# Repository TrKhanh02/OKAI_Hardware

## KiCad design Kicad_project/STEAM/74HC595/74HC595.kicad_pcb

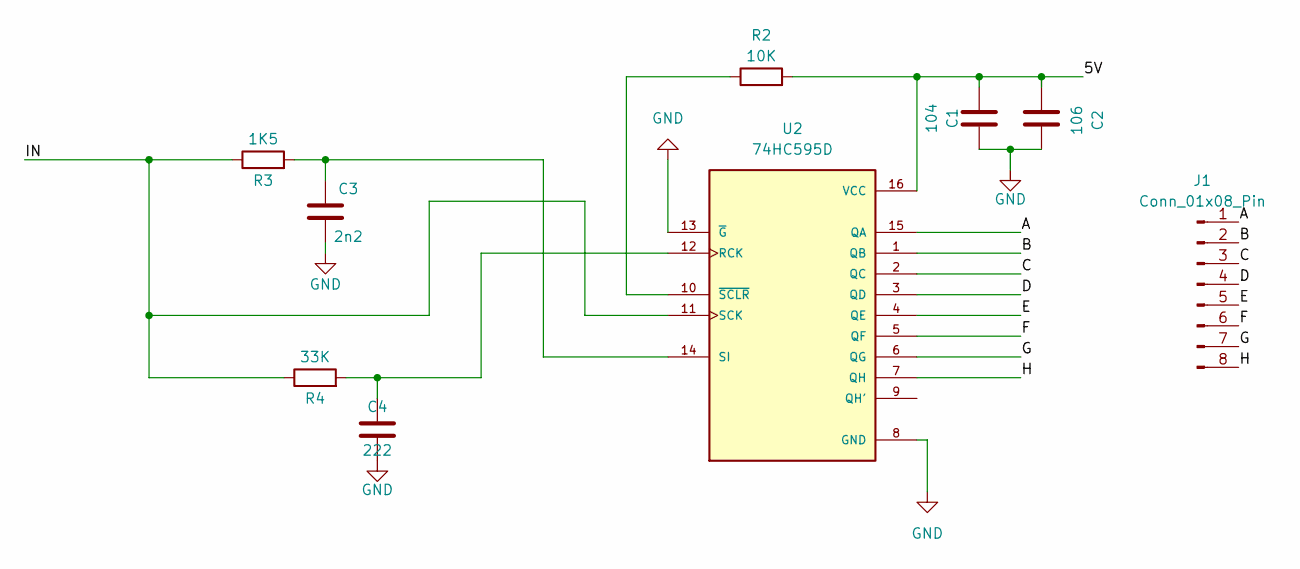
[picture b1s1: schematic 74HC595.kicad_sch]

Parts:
C1: 104; C_0805_2012Metric
C2: 106; C_0805_2012Metric
C3: 2n2; C_0805_2012Metric
C4: 222; C_0805_2012Metric
J1: Conn_01x08_Pin; PinHeader_1x08_P2.54mm_Vertical
R2: 10K; R_0805_2012Metric
R3: 1K5; R_0805_2012Metric
R4: 33K; R_0805_2012Metric
U2: 74HC595D; SOP127P600X175-16N; PARTREV 4.0

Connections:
/5V: C1.1, C2.1, R2.2, U2.16 (VCC)
/A: J1.1, U2.15 (QA)
/B: J1.2, U2.1 (QB)
/C: J1.3, U2.2 (QC)
/D: J1.4, U2.3 (QD)
/E: J1.5, U2.4 (QE)
/F: J1.6, U2.5 (QF)
/G: J1.7, U2.6 (QG)
/H: J1.8, U2.7 (QH)
/IN: R3.1, R4.1, U2.11 (SCK)
GND: C1.2, C2.2, C3.1, C4.1, U2.8 (GND), U2.13 (~G)
unnamed: C4.2, R4.2, U2.12 (RCK)
unnamed: C3.2, R3.2, U2.14 (SI)
unnamed: R2.1, U2.10 (~SCLR)

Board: 2 copper layers, 9 parts (0 on the bottom side), 14 nets, no tracks yet.

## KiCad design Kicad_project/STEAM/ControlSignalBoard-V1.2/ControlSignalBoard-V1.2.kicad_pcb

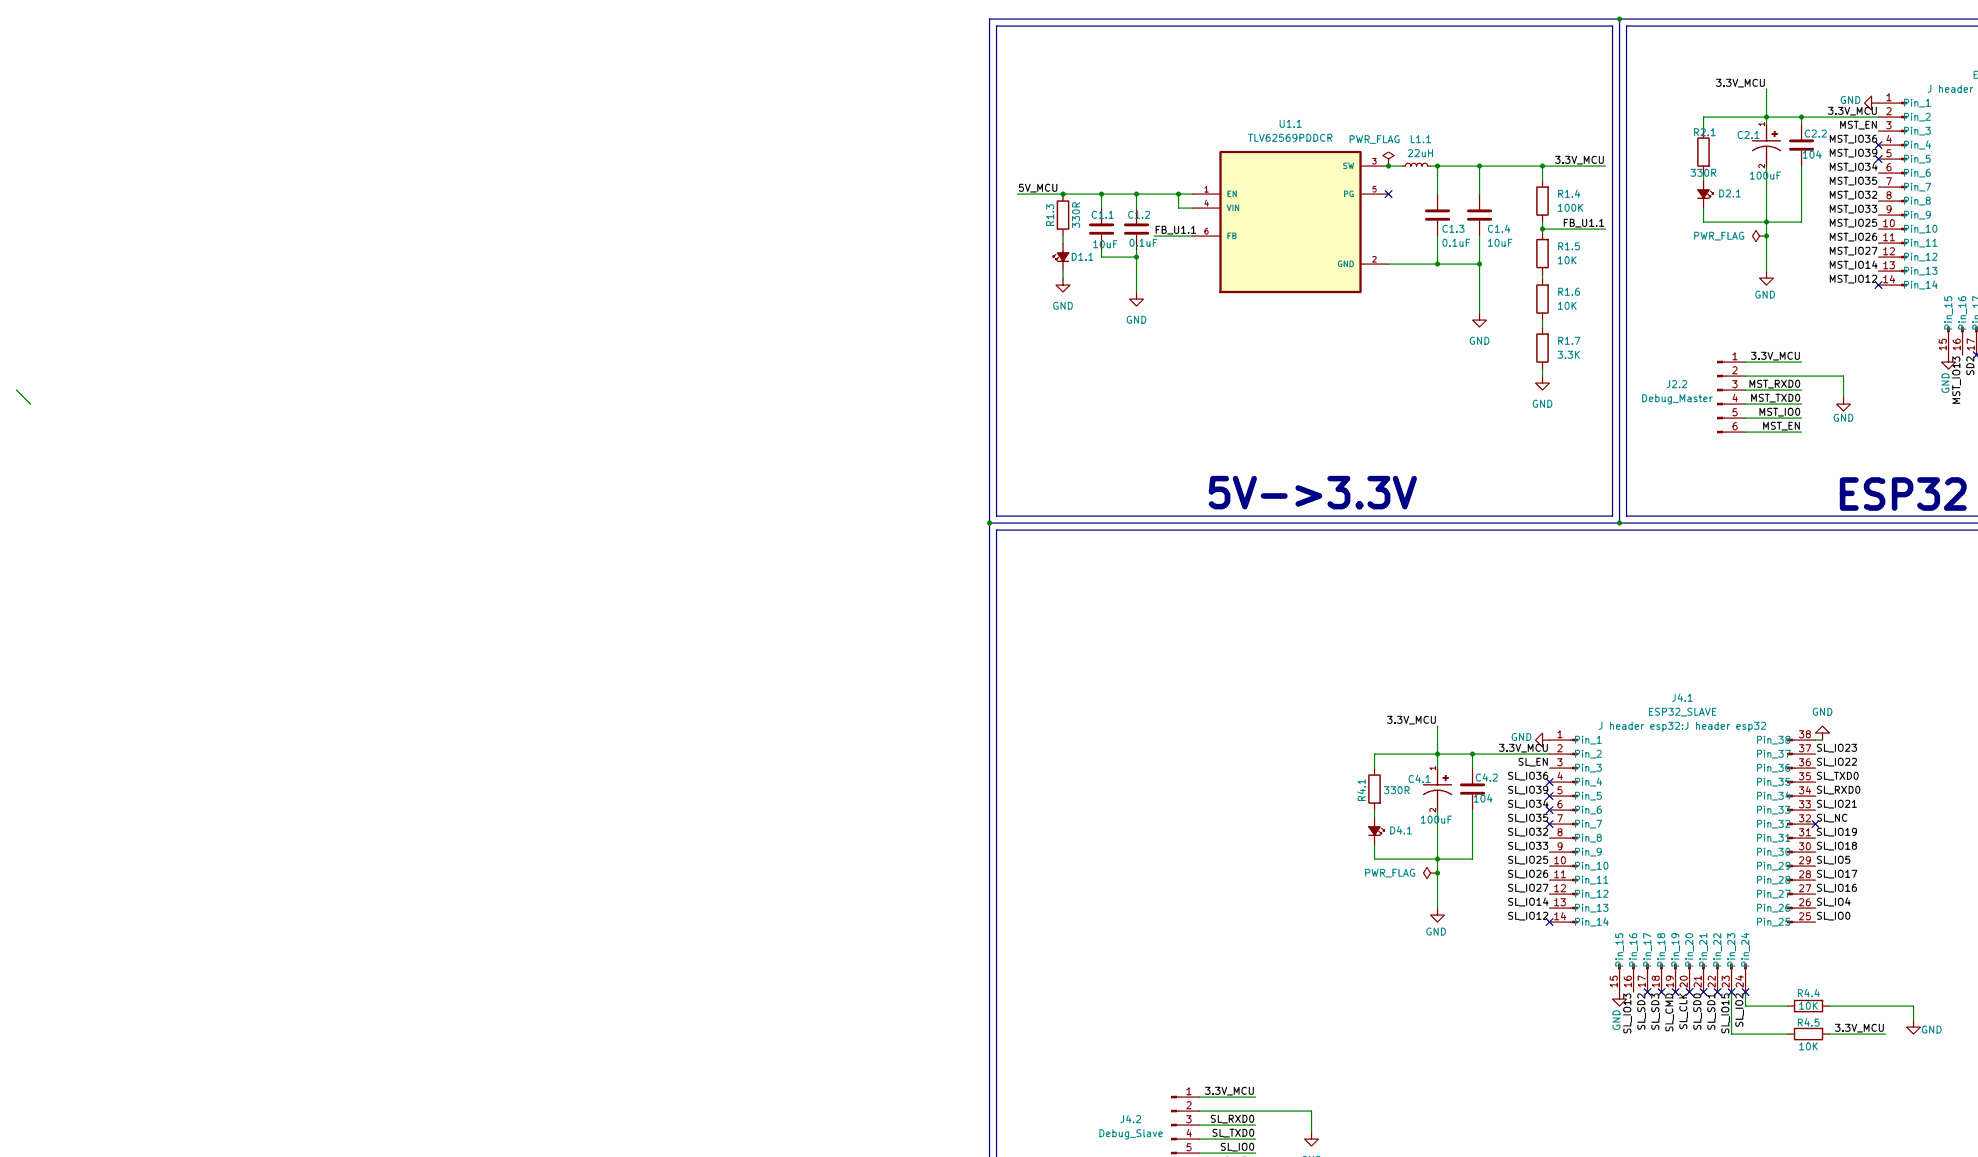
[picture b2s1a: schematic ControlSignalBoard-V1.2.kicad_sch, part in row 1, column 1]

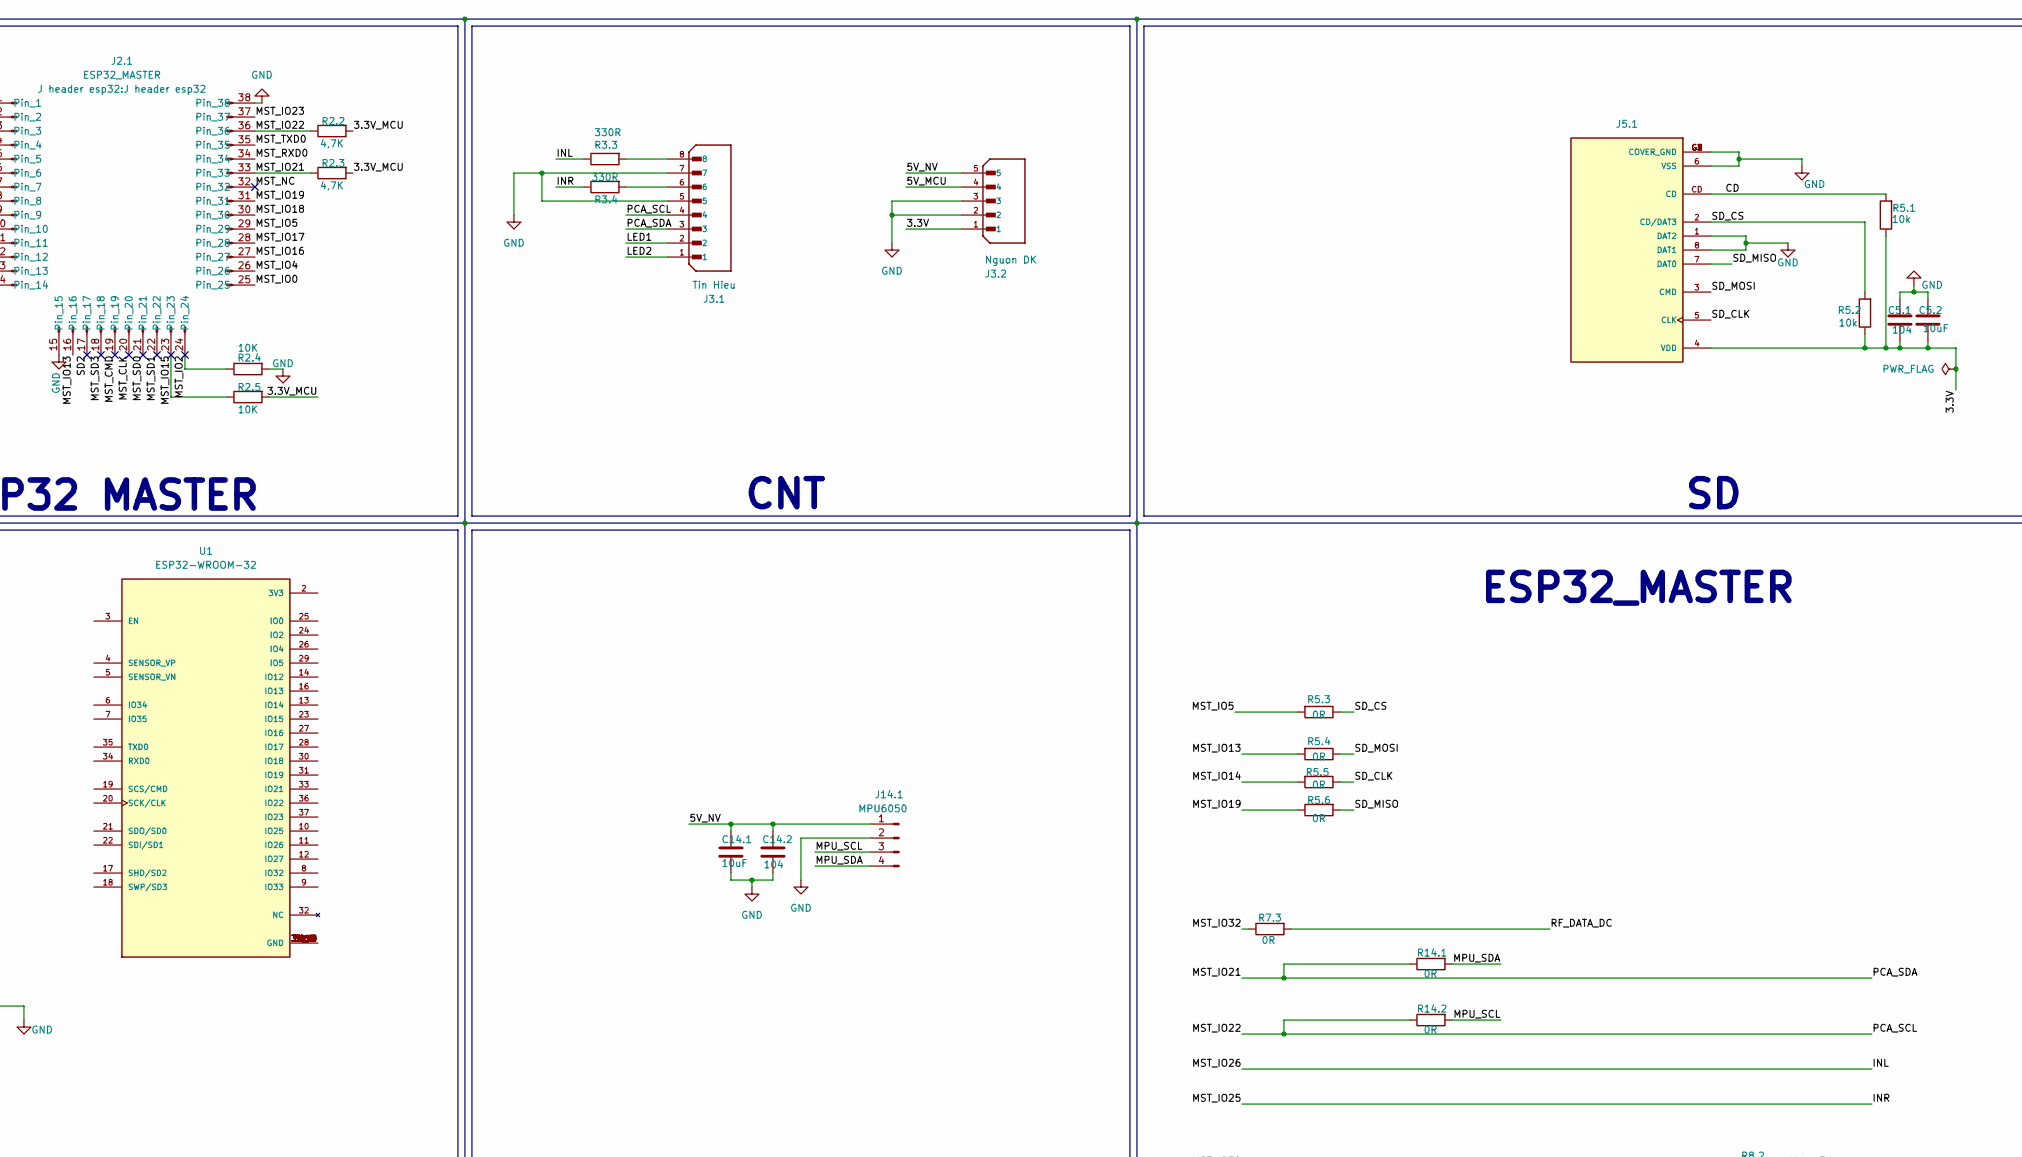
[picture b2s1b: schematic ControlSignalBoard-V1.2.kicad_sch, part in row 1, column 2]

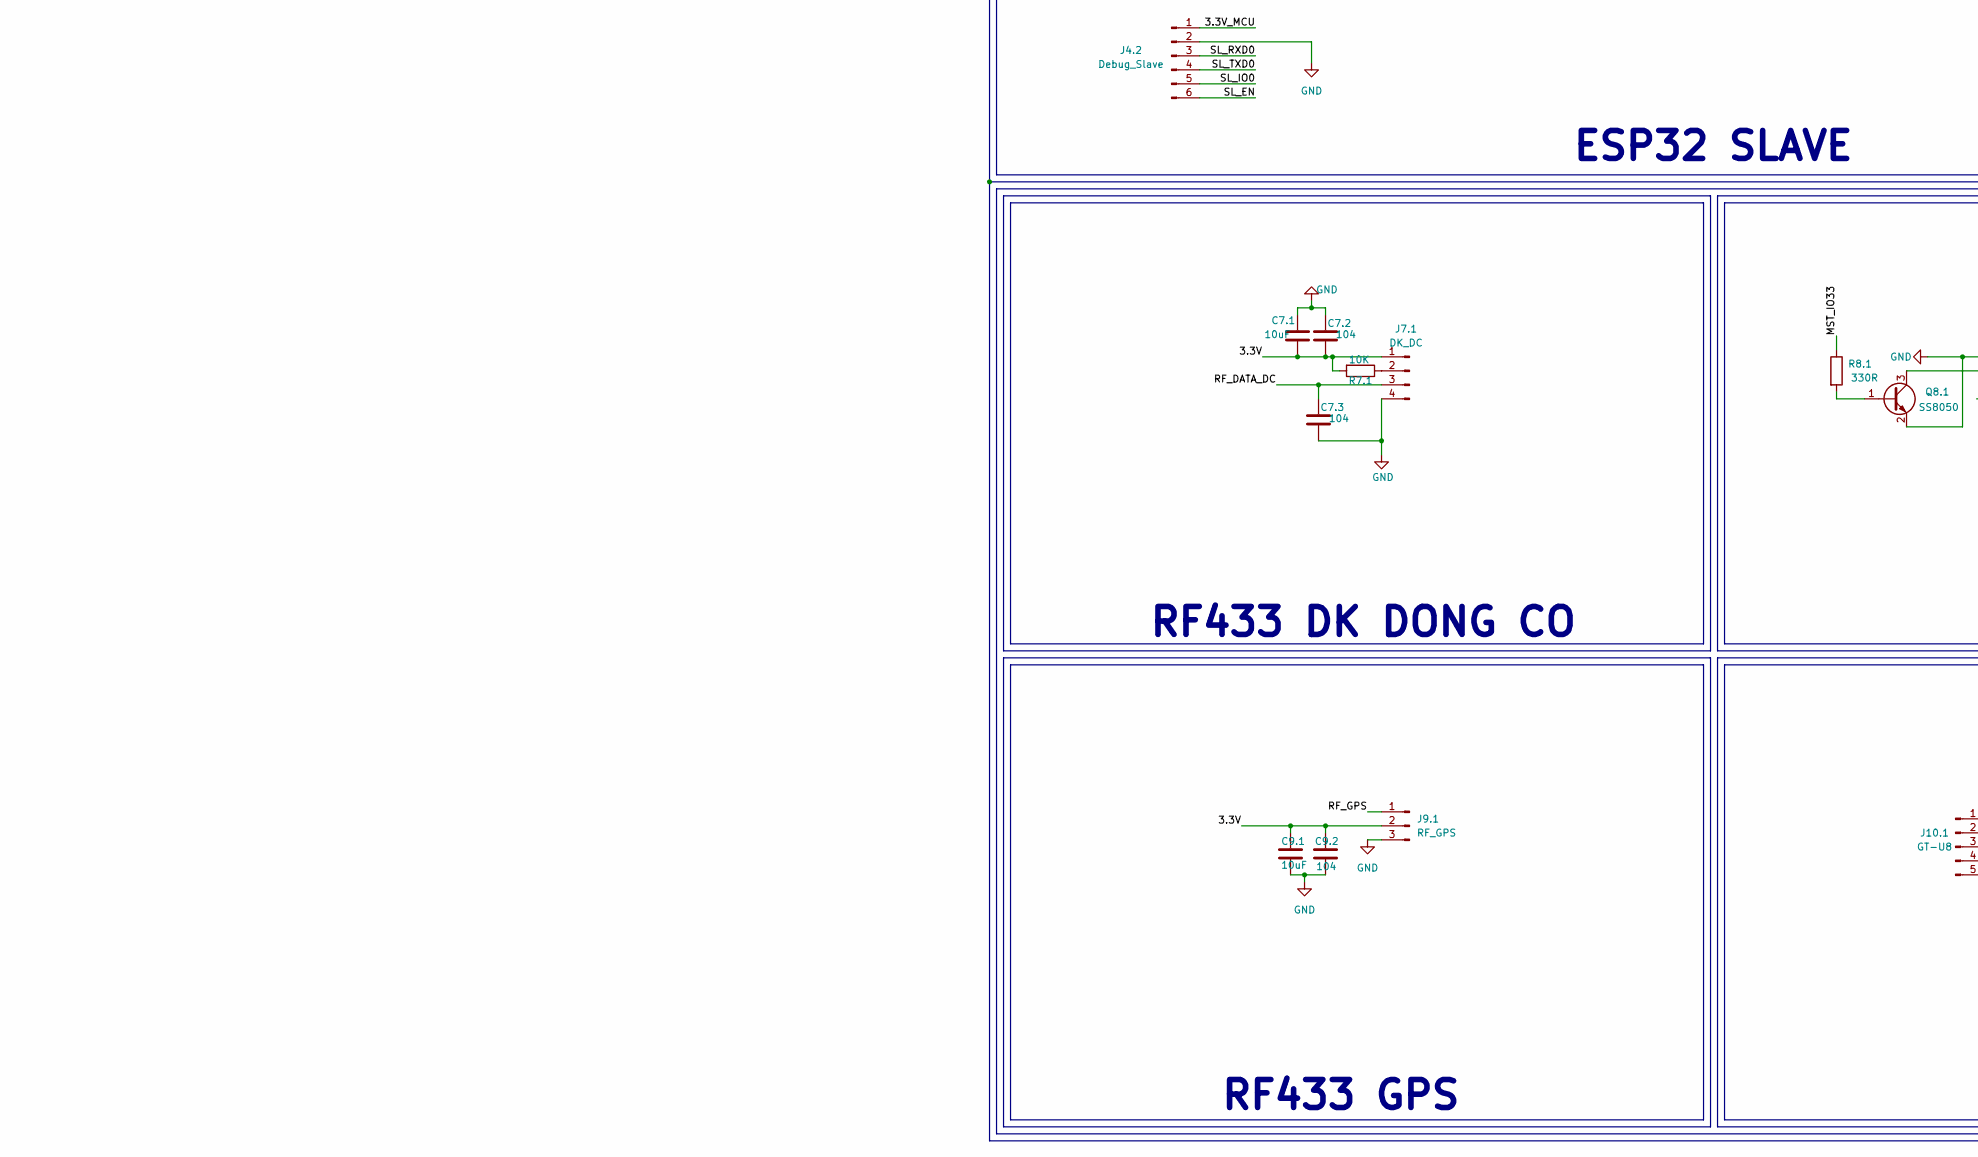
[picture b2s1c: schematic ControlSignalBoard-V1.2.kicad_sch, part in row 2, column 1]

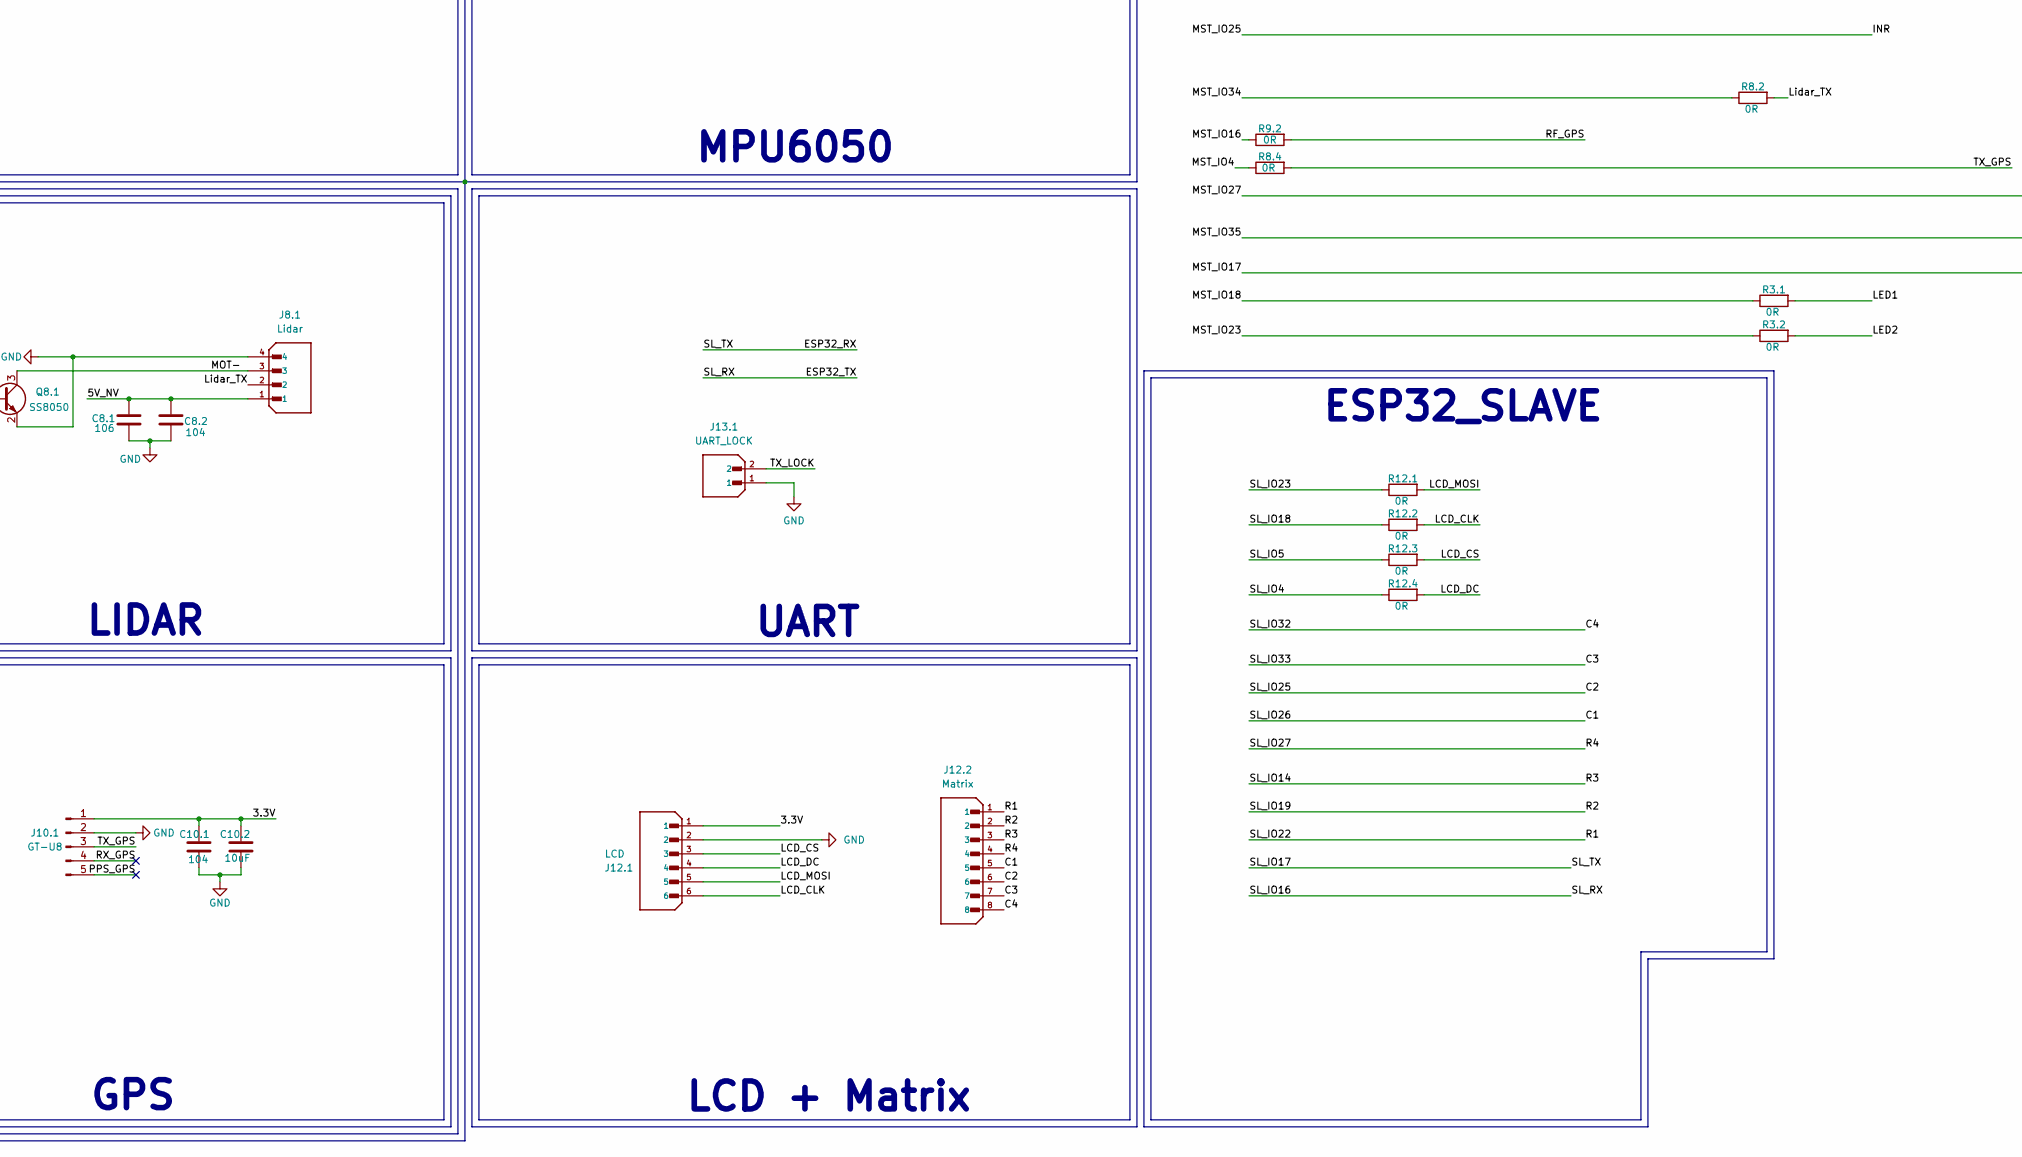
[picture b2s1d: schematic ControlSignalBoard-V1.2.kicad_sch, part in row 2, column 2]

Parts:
C1.1, C1.4: 10uF; C_0805_2012Metric
C1.2, C1.3: 0.1uF; C_0805_2012Metric
C2.1, C4.1: 100uF; CAPMP3216X180N; PARTREV 031320
C2.2, C4.2, C5.1, C7.2, C7.3, C8.2, C9.2, C10.1, C14.2: 104; C_0805_2012Metric_Pad1.18x1.45mm_HandSolder
C5.2, C7.1, C9.1, C10.2, C14.1: 10uF; C_0805_2012Metric_Pad1.18x1.45mm_HandSolder
C8.1: 106; C_0805_2012Metric_Pad1.18x1.45mm_HandSolder
D1.1, D2.1, D4.1: LED_Small_Filled; LED_0805_2012Metric_Pad1.15x1.40mm_HandSolder
J2.1: ESP32_MASTER; J header esp32
J2.2: Debug_Master; PinSocket_1x06_P2.54mm_Vertical
J3.1: Tin Hieu; JST_B8B-XH-A_LF__SN_; PARTREV 7/4/21
J3.2: Nguon DK; JST_B5B-XH-A; PARTREV 7/4/21
J4.1: ESP32_SLAVE; J header esp32
J4.2: Debug_Slave; PinSocket_1x06_P2.54mm_Vertical
J5.1: SD; CUI_MSD-1-A; PARTREV 1.0
J7.1: DK_DC; PinSocket_1x04_P2.54mm_Vertical
J8.1: Lidar; JST_B4B-XH-A_LF__SN_; PARTREV 7/4/21
J9.1: RF_GPS; PinSocket_1x03_P2.54mm_Vertical
J10.1: GT-U8; PinSocket_1x05_P2.54mm_Vertical
J12.1: LCD; JST_B6B-XH-A_LF__SN_; PARTREV 7/4/21
J12.2: Matrix; JST_B8B-XH-A_LF__SN_; PARTREV 7/4/21
J13.1: UART_LOCK; JST_B2B-XH-A_LF__SN_; PARTREV N/A
J14.1: MPU6050; PinSocket_1x04_P2.54mm_Vertical
L1.1: 22uH; L_Ferrocore_DLG-0705
Q8.1: SS8050; SOT-23
R1.3, R2.1, R3.3, R3.4, R4.1, R8.1: 330R; R_0805_2012Metric_Pad1.20x1.40mm_HandSolder
R1.4: 100K; R_0805_2012Metric
R1.5, R1.6: 10K; R_0805_2012Metric
R1.7: 3.3K; R_0805_2012Metric
R2.2, R2.3: 4,7K; R_0805_2012Metric_Pad1.20x1.40mm_HandSolder
R2.4, R2.5, R4.4, R4.5, R7.1: 10K; R_0805_2012Metric_Pad1.20x1.40mm_HandSolder
R3.1, R3.2, R5.3, R5.4, R5.5, R5.6, R7.3, R8.2, R8.4, R9.2, R12.1, R12.2, R12.3, R12.4, R14.1, R14.2: 0R; R_0805_2012Metric_Pad1.20x1.40mm_HandSolder
R5.1, R5.2: 10k; R_0805_2012Metric_Pad1.20x1.40mm_HandSolder
U1: ESP32-WROOM-32; MODULE_ESP32-WROOM-32
U1.1: TLV62569PDDCR; SOT95P280X110-6N

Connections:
/3.3V: C5.1.1, C5.2.1, C7.1.2, C7.2.2, C9.1.1, C9.2.1, C10.1.1, C10.2.1, J3.2.1, J5.1.4 (VDD), J7.1.1, J9.1.2, J10.1.1, J12.1.1, R5.1.1, R5.2.1, R7.1.2
/3.3V_MCU: C1.3.1, C1.4.1, C2.1.1, C2.2.1, C4.1.1, C4.2.1, J2.1.2, J2.2.1, J4.1.2, J4.2.1, L1.1.1, R1.4.2, R2.1.1, R2.2.2, R2.3.2, R2.5.2, R4.1.1, R4.5.2
/5V_MCU: C1.1.1, C1.2.1, J3.2.4, R1.3.1, U1.1.1 (EN), U1.1.4 (VIN)
/5V_NV: C8.1.1, C8.2.1, C14.1.1, C14.2.1, J3.2.5, J8.1.1, J14.1.1
/C1: J4.1.11, J12.2.5
/C2: J4.1.10, J12.2.6
/C3: J4.1.9, J12.2.7
/C4: J4.1.8, J12.2.8
/CD: J5.1.CD, R5.1.2
/ESP32_RX: J2.1.7, J4.1.28
/ESP32_TX: J2.1.12, J4.1.27
/FB_U1.1: R1.4.1, R1.5.2, U1.1.6 (FB)
/INL: J2.1.11, R3.3.1
/INR: J2.1.10, R3.4.1
/LCD_CLK: J12.1.6, R12.2.2
/LCD_CS: J12.1.3, R12.3.2
/LCD_DC: J12.1.4, R12.4.2
/LCD_MOSI: J12.1.5, R12.1.2
/LED1: J3.1.2, R3.1.2
/LED2: J3.1.1, R3.2.2
/Lidar_TX: J8.1.2, R8.2.2
/MOT-: J8.1.3, Q8.1.3 (C)
/MPU_SCL: J14.1.3, R14.2.2
/MPU_SDA: J14.1.4, R14.1.2
/MST_CLK: J2.1.20
/MST_CMD: J2.1.19
/MST_EN: J2.1.3, J2.2.6
/MST_IO0: J2.1.25, J2.2.5
/MST_IO2: J2.1.24, R2.4.1
/MST_IO4: J2.1.26, R8.4.1
/MST_IO5: J2.1.29, R5.3.2; also elsewhere on the board
/MST_IO12: J2.1.14
/MST_IO13: J2.1.16, R5.4.2; also elsewhere on the board
/MST_IO14: J2.1.13, R5.5.2; also elsewhere on the board
/MST_IO15: J2.1.23, R2.5.1
/MST_IO16: J2.1.27, R9.2.1
/MST_IO17: J2.1.28, J13.1.2
/MST_IO18: J2.1.30, R3.1.1
/MST_IO19: J2.1.31, R5.6.1; also elsewhere on the board
/MST_IO21: J2.1.33, J3.1.3, R2.3.1, R14.1.1
/MST_IO22: J2.1.36, J3.1.4, R2.2.1, R14.2.1
/MST_IO23: J2.1.37, R3.2.1
/MST_IO32: J2.1.8, R7.3.1
/MST_IO33: J2.1.9, R8.1.1
/MST_IO34: J2.1.6, R8.2.1
/MST_IO36: J2.1.4
/MST_IO39: J2.1.5
/MST_NC: J2.1.32
/MST_RXD0: J2.1.34, J2.2.3
/MST_SD0: J2.1.21
/MST_SD1: J2.1.22
/MST_SD3: J2.1.18
/MST_TXD0: J2.1.35, J2.2.4
/PPS_GPS: J10.1.5
/R1: J4.1.36, J12.2.1
/R2: J4.1.31, J12.2.2
/R3: J4.1.13, J12.2.3
/R4: J4.1.12, J12.2.4
/RF_DATA_DC: C7.3.1, J7.1.3, R7.3.2
/RF_GPS: J9.1.1, R9.2.2
/RX_GPS: J10.1.4
/SD2: J2.1.17
/SD_CLK: J5.1.5 (CLK), R5.5.1; also elsewhere on the board
/SD_CS: J5.1.2 (CD/DAT3), R5.2.2, R5.3.1; also elsewhere on the board
/SD_MISO: J5.1.7 (DAT0), R5.6.2; also elsewhere on the board
/SD_MOSI: J5.1.3 (CMD), R5.4.1; also elsewhere on the board
/SL_CLK: J4.1.20
/SL_CMD: J4.1.19
/SL_EN: J4.1.3, J4.2.6
/SL_IO0: J4.1.25, J4.2.5
/SL_IO2: J4.1.24, R4.4.1
/SL_IO4: J4.1.26, R12.4.1
/SL_IO5: J4.1.29, R12.3.1
/SL_IO12: J4.1.14
/SL_IO13: J4.1.16
/SL_IO15: J4.1.23, R4.5.1
/SL_IO18: J4.1.30, R12.2.1
/SL_IO21: J4.1.33
/SL_IO23: J4.1.37, R12.1.1
/SL_IO34: J4.1.6
/SL_IO35: J4.1.7
/SL_IO36: J4.1.4
/SL_IO39: J4.1.5
/SL_NC: J4.1.32
/SL_RXD0: J4.1.34, J4.2.3
/SL_SD0: J4.1.21
/SL_SD1: J4.1.22
/SL_SD2: J4.1.17
/SL_SD3: J4.1.18
/SL_TXD0: J4.1.35, J4.2.4
/TX_GPS: J10.1.3, R8.4.2
GND: C1.1.2, C1.2.2, C1.3.2, C1.4.2, C2.1.2, C2.2.2, C4.1.2, C4.2.2, C5.1.2, C5.2.2, C7.1.1, C7.2.1, C7.3.2, C8.1.2, C8.2.2, C9.1.2, C9.2.2, C10.1.2, C10.2.2, C14.1.2, C14.2.2, D1.1.1 (K), D2.1.1 (K), D4.1.1 (K), J2.1.1, J2.1.15, J2.1.38, J2.2.2, J3.1.5, J3.1.7, J3.2.2, J3.2.3, J4.1.1, J4.1.15, J4.1.38, J4.2.2, J5.1.1 (DAT2), J5.1.6 (VSS), J5.1.8 (DAT1), J5.1.G1 (COVER_GND), J5.1.G2 (COVER_GND), J5.1.G3 (COVER_GND), J5.1.G4 (COVER_GND), J7.1.4, J8.1.4, J9.1.3, J10.1.2, J12.1.2, J13.1.1, J14.1.2, Q8.1.2 (E), R1.7.1, R2.4.2, R4.4.2, U1.1.2 (GND)
unnamed: D1.1.2 (A), R1.3.2
unnamed: D2.1.2 (A), R2.1.2
unnamed: D4.1.2 (A), R4.1.2
unnamed: J3.1.6, R3.4.2
unnamed: J3.1.8, R3.3.2
unnamed: J7.1.2, R7.1.1
unnamed: Q8.1.1 (B), R8.1.2
unnamed: R1.5.1, R1.6.2
unnamed: R1.6.1, R1.7.2
unnamed: U1.1 (GND), U1.15 (GND), U1.38 (GND), U1.39_1 (GND), U1.39_2 (GND), U1.39_3 (GND), U1.39_4 (GND), U1.39_5 (GND), U1.39_6 (GND), U1.39_7 (GND), U1.39_8 (GND), U1.39_9 (GND), U1.39_10 (GND), U1.39_11 (GND), U1.39_12 (GND), U1.39_13 (GND), U1.39_14 (GND), U1.39_15 (GND), U1.39_16 (GND), U1.39_17 (GND), U1.39_18 (GND), U1.39_19 (GND), U1.39_20 (GND), U1.39_21 (GND)
unnamed: L1.1.2, U1.1.3 (SW)

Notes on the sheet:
CNT
ESP32 SLAVE
ESP32_SLAVE
RF433 GPS
LIDAR
ESP32_MASTER
MPU6050
LCD + Matrix
5V->3.3V
UART
GPS
ESP32 MASTER
RF433 DK DONG CO

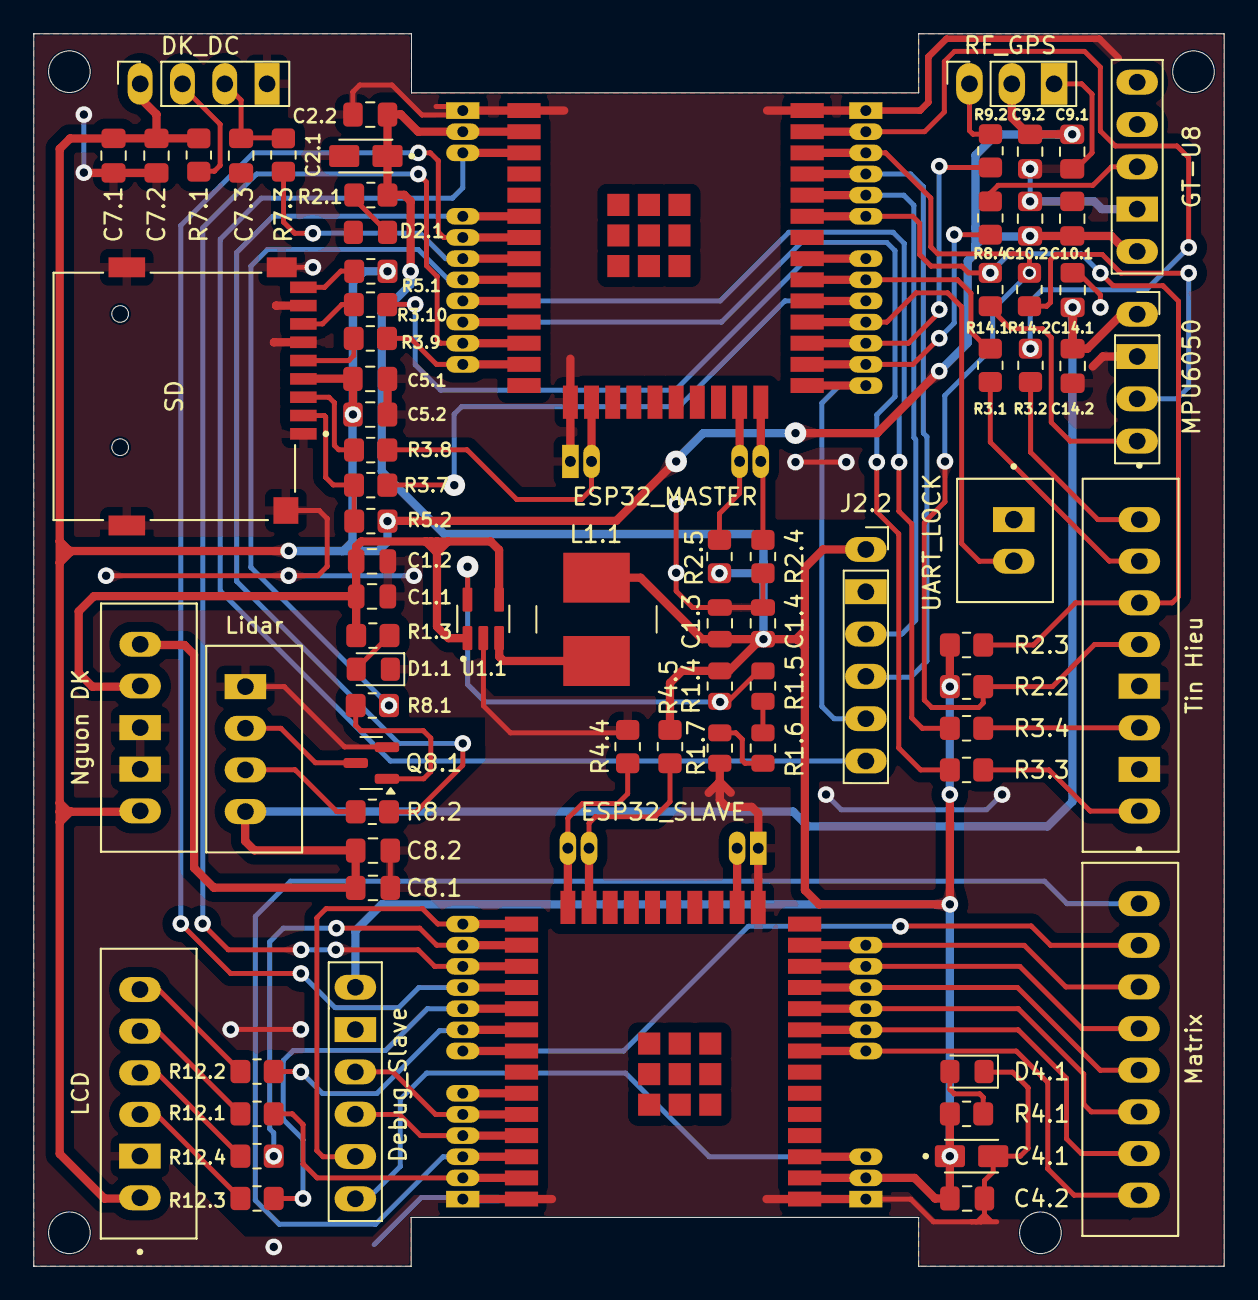
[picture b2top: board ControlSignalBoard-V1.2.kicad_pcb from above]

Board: 2 copper layers, 71.5 x 74.0 mm, 77 parts (0 on the bottom side), 76 nets.

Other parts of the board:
R3.7, R3.8, R3.9, R3.10: 0R; R_0805_2012Metric_Pad1.20x1.40mm_HandSolder

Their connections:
/MST_IO5: R3.7.2; also elsewhere on the board
/MST_IO13: R3.8.2; also elsewhere on the board
/MST_IO14: R3.9.2; also elsewhere on the board
/MST_IO19: R3.10.1; also elsewhere on the board
/SD_CLK: R3.9.1; also elsewhere on the board
/SD_CS: R3.7.1; also elsewhere on the board
/SD_MISO: R3.10.2; also elsewhere on the board
/SD_MOSI: R3.8.1; also elsewhere on the board
